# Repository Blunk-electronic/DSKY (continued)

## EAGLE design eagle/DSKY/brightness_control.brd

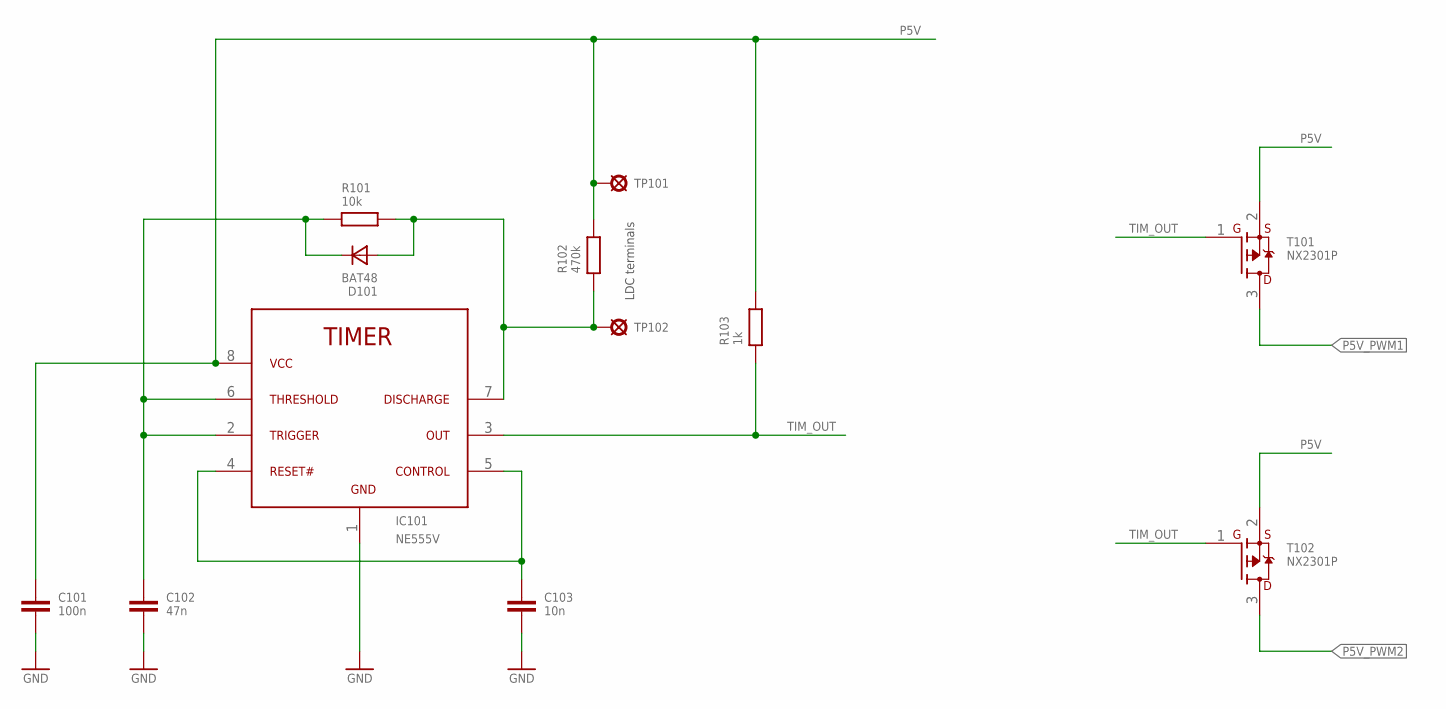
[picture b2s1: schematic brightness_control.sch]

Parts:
C101: 100n; S_0805; PART_CODE_BEL C_PAC_S_0805_VAL_100n
C102: 47n; S_0805; PART_CODE_BEL C_PAC_S_0805_VAL_47n
C103: 10n; S_0805; PART_CODE_BEL C_PAC_S_0805_VAL_10n
D101: BAT48; T_DO204_GRID_10MM
IC101: NE555V; T_NDIP8; PART_CODE_BEL IC_PAC_T_NDIP8_VAL_NE555V
R101: 10k; S_0805; PART_CODE_BEL R_PAC_S_0805_VAL_10k
R102: 470k; S_0805; PART_CODE_BEL R_PAC_S_0805_VAL_470k
R103: 1k; S_0805; PART_CODE_BEL R_PAC_S_0805_VAL_1k
T101, T102: NX2301P; S_SOT23; PART_CODE_BEL T_PAC_S_SOT23_VAL_NX2301P
TP101, TP102: TEST_POINT_T_LARGE; T_TEST_POINT_LARGE

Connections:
GND: C101.2, C102.2, C103.2, IC101.1 (GND)
P5V: C101.1, IC101.8 (VCC), R102.2, R103.2, T101.2 (S), T102.2 (S), TP101.1
P5V_PWM1: T101.3 (D)
P5V_PWM2: T102.3 (D)
TIM_1: C103.1, IC101.4 (RST#), IC101.5 (OC)
TIM_2: C102.1, D101.C, IC101.2 (TRG), IC101.6 (TRSHLD), R101.1
TIM_3: D101.A, IC101.7 (DSCHRG), R101.2, R102.1, TP102.1
TIM_OUT: IC101.3 (OUT), R103.1, T101.1 (G), T102.1 (G)

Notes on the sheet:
LDC terminals

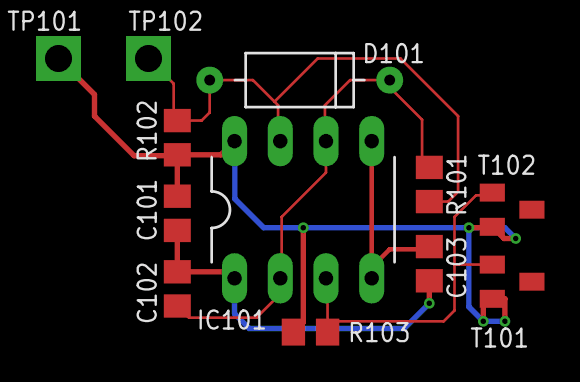
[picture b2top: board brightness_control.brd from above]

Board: 2 copper layers, 12 parts (0 on the bottom side), 6 nets.

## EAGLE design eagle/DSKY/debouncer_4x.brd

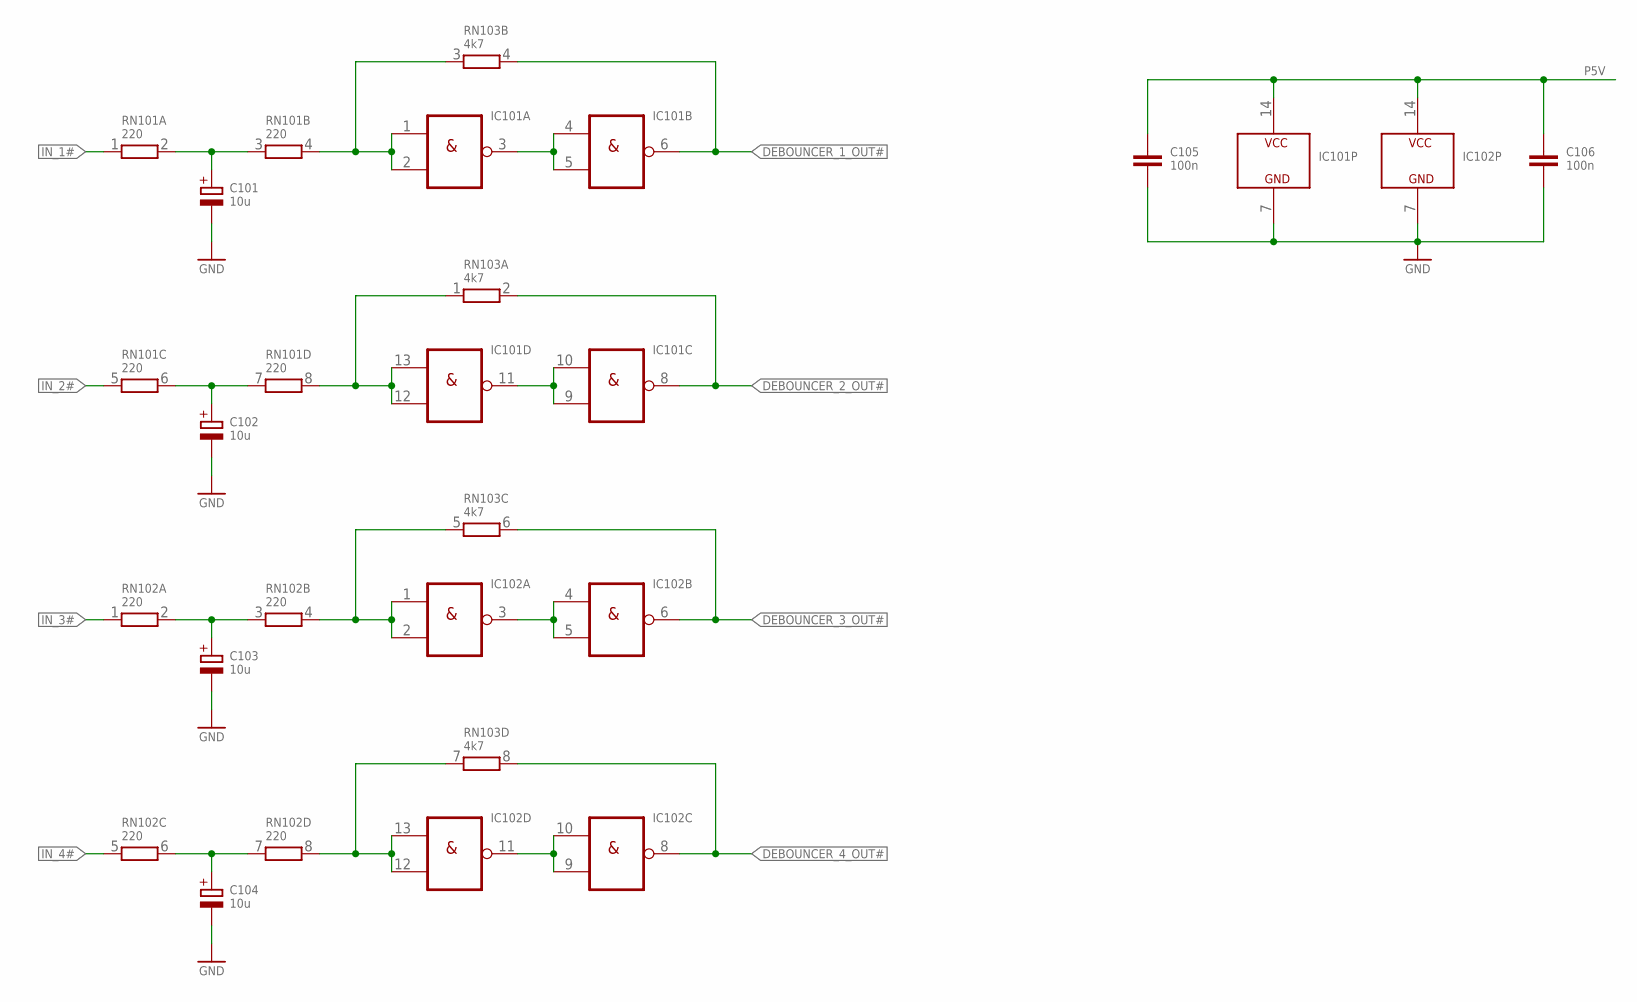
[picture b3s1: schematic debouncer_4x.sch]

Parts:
C101, C102, C103, C104: 10u; T_RADIAL_5MM_GRID_2.54MM; PART_CODE_BEL C_PAC_T_RADIAL_5mm_GRID_2.54mm_VAL_10u_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
C105, C106: 100n; S_0805; PART_CODE_BEL C_PAC_S_0805_VAL_100n
IC101, IC102: 7400N; T_NDIP14
RN101, RN102: 220; T_SIL8
RN103: 4k7; T_SIL8; PART_CODE_BEL RN_PAC_T_SIL8_VAL_4k7

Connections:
DEBOUNCER_1_OUT#: IC101.6 (O), RN103.4 (2)
DEBOUNCER_2_OUT#: IC101.8 (O), RN103.2
DEBOUNCER_3_OUT#: IC102.6 (O), RN103.6 (2)
DEBOUNCER_4_OUT#: IC102.8 (O), RN103.8 (2)
DEBOUNCER_10: C101.+, RN101.2, RN101.3 (1)
DEBOUNCER_11: IC101.1 (I0), IC101.2 (I1), RN101.4 (2), RN103.3 (1)
DEBOUNCER_12: IC101.3 (O), IC101.4 (I0), IC101.5 (I1)
DEBOUNCER_20: C102.+, RN101.6 (2), RN101.7 (1)
DEBOUNCER_21: IC101.12 (I1), IC101.13 (I0), RN101.8 (2), RN103.1
DEBOUNCER_22: IC101.9 (I1), IC101.10 (I0), IC101.11 (O)
DEBOUNCER_30: C103.+, RN102.2, RN102.3 (1)
DEBOUNCER_31: IC102.1 (I0), IC102.2 (I1), RN102.4 (2), RN103.5 (1)
DEBOUNCER_32: IC102.3 (O), IC102.4 (I0), IC102.5 (I1)
DEBOUNCER_40: C104.+, RN102.6 (2), RN102.7 (1)
DEBOUNCER_41: IC102.12 (I1), IC102.13 (I0), RN102.8 (2), RN103.7 (1)
DEBOUNCER_42: IC102.9 (I1), IC102.10 (I0), IC102.11 (O)
GND: C101.-, C102.-, C103.-, C104.-, C105.2, C106.2, IC101.7 (GND), IC102.7 (GND)
IN_1#: RN101.1
IN_2#: RN101.5 (1)
IN_3#: RN102.1
IN_4#: RN102.5 (1)
P5V: C105.1, C106.1, IC101.14 (VCC), IC102.14 (VCC)

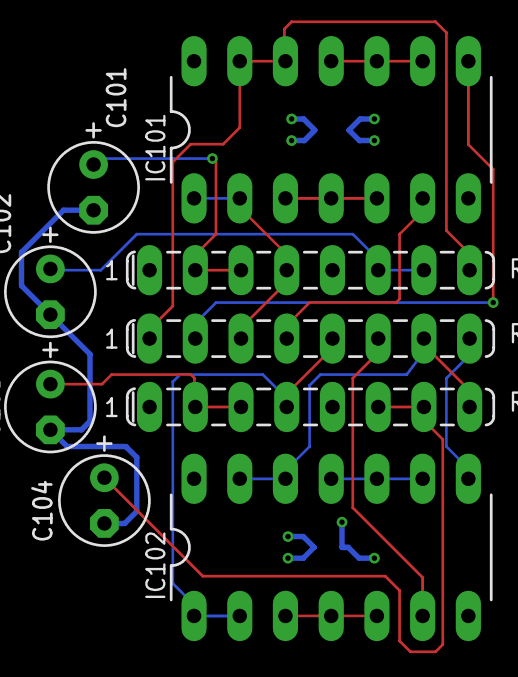
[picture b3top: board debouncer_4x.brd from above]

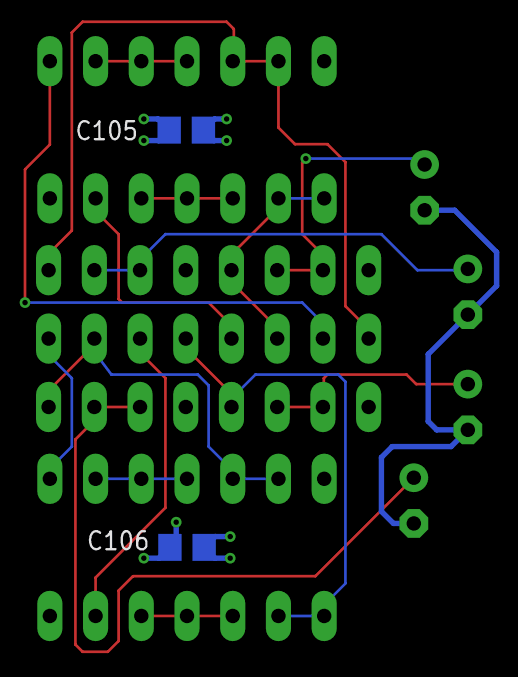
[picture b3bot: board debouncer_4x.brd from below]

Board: 2 copper layers, 11 parts (2 on the bottom side), 18 nets.

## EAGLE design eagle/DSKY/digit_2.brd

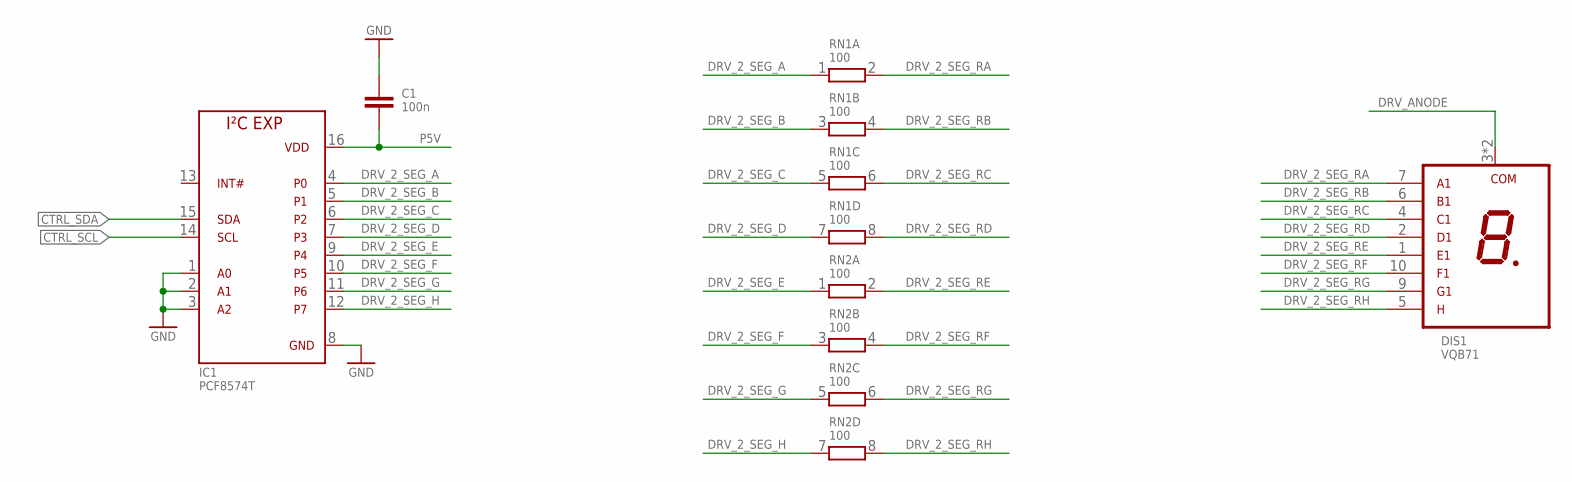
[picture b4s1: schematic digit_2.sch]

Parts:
C1: 100n; S_0805; PART_CODE_BEL C_PAC_S_0805_VAL_100n
DIS1: VQB71; T_VQB71
IC1: PCF8574T; S_SOIC16
RN1, RN2: 100; T_SIL8; PART_CODE_BEL RN_PAC_T_SIL8_VAL_100

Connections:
CTRL_SCL: IC1.14 (SCL)
CTRL_SDA: IC1.15 (SDA)
DRV_2_SEG_A: IC1.4 (P0), RN1.1
DRV_2_SEG_B: IC1.5 (P1), RN1.3 (1)
DRV_2_SEG_C: IC1.6 (P2), RN1.5 (1)
DRV_2_SEG_D: IC1.7 (P3), RN1.7 (1)
DRV_2_SEG_E: IC1.9 (P4), RN2.1
DRV_2_SEG_F: IC1.10 (P5), RN2.3 (1)
DRV_2_SEG_G: IC1.11 (P6), RN2.5 (1)
DRV_2_SEG_H: IC1.12 (P7), RN2.7 (1)
DRV_2_SEG_RA: DIS1.7 (A1), RN1.2
DRV_2_SEG_RB: DIS1.6 (B1), RN1.4 (2)
DRV_2_SEG_RC: DIS1.4 (C1), RN1.6 (2)
DRV_2_SEG_RD: DIS1.2 (D1), RN1.8 (2)
DRV_2_SEG_RE: DIS1.1 (E1), RN2.2
DRV_2_SEG_RF: DIS1.10 (F1), RN2.4 (2)
DRV_2_SEG_RG: DIS1.9 (G1), RN2.6 (2)
DRV_2_SEG_RH: DIS1.5 (DP1), RN2.8 (2)
DRV_ANODE: DIS1.3 (COM1), DIS1.8 (COM1)
GND: C1.1, IC1.1 (A0), IC1.2 (A1), IC1.3 (A2), IC1.8 (GND)
P5V: C1.2, IC1.16 (VDD)

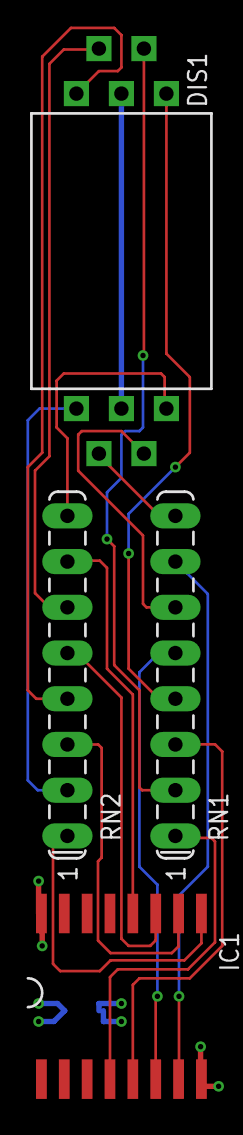
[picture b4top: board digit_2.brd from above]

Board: 2 copper layers, 5 parts (1 on the bottom side), 19 nets.

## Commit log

2015-10-14 started display
2015-10-14 added gitignore file
2015-10-14 moved ignore file to root directory
2015-10-15 brightness control
2015-10-15 added connectors
2015-10-16 reverse voltage protection
2015-10-16 prepared routing of P5V and GND
2015-10-19 silk screen for keys fixed
2015-10-19 fixed attributes
2015-10-26 -routed supply -applied dru Q-Print standard
2015-10-27 fixed silk screen issues
2015-11-23 front panel drawing
2016-03-17 removed eagle.epf.in from .gitignore
2016-07-28 added variable for base directory
2016-07-29 added lck file
2016-07-29 added readme in bom dir
2016-07-29 added CAM archives (for demo only)
2016-07-29 fixed cam archives
2016-07-30 removed useless layers
2018-05-15 cleaned up
2019-08-27 change scriipt dir
2020-03-20 add img
2020-04-04 add photo rack
2020-04-04 link to image
